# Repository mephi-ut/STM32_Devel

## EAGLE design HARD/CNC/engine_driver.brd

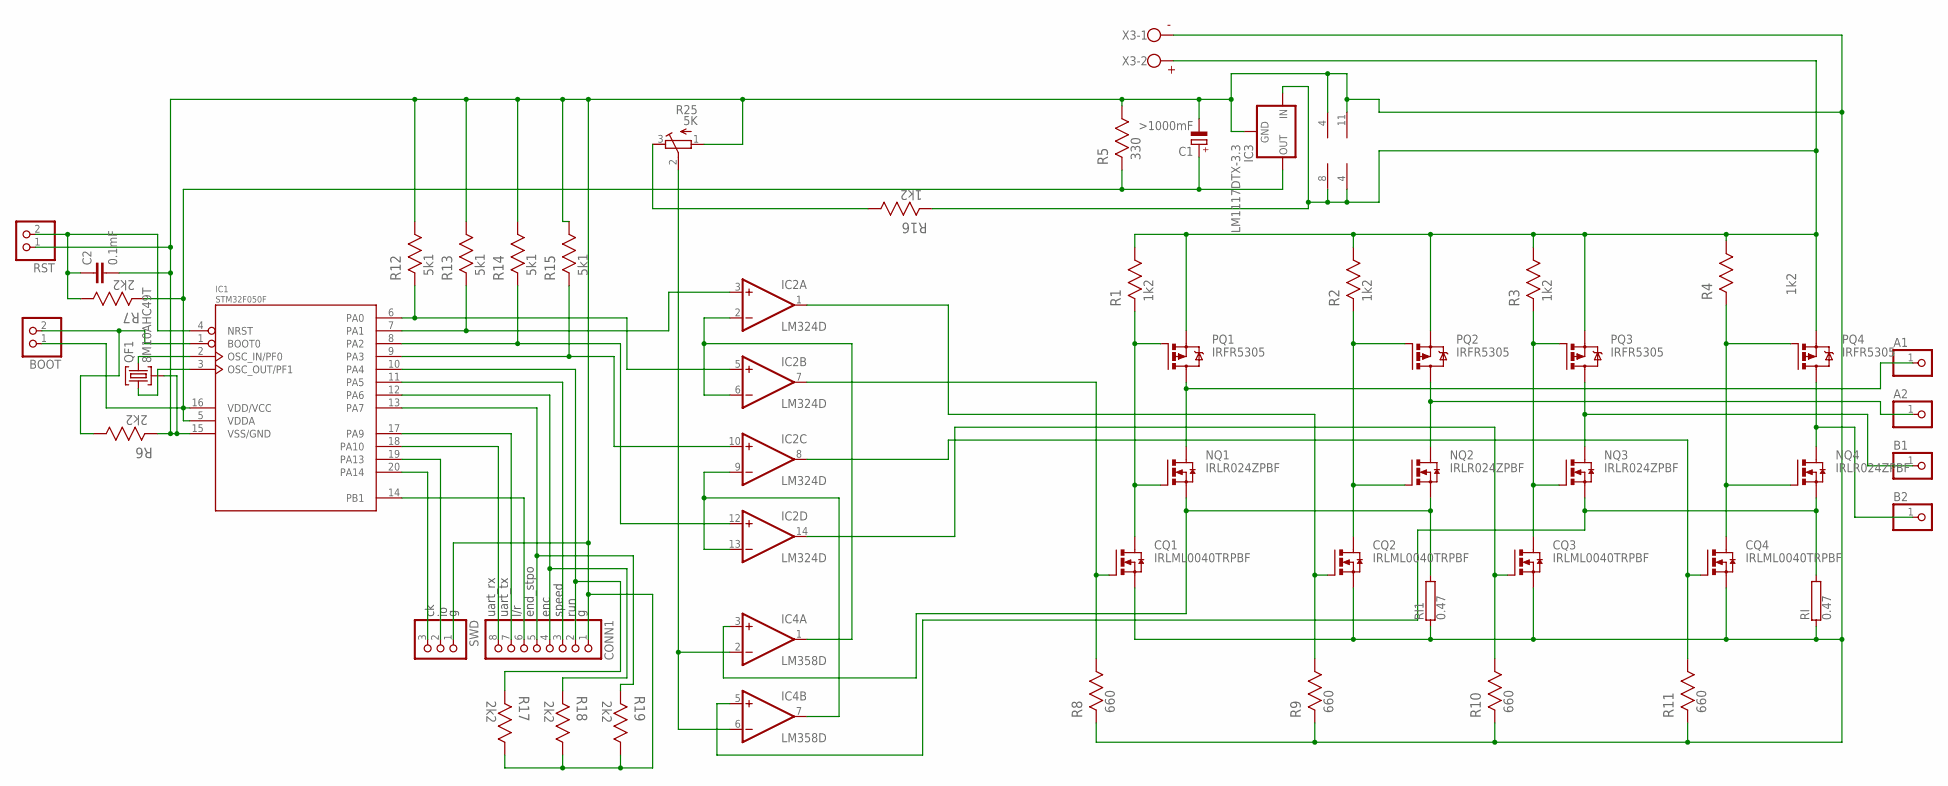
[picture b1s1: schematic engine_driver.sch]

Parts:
A1, A2: PINHD-1X1; 1X01
B1, B2: PINHD-1X1; 1X01
BOOT: PINHD-1X2; 1X02
C1: >1000mF; E2-5
C2: 0.1mF; C1206
CONN1: PINHD-1X8; 1X08
CQ1, CQ2, CQ3, CQ4: IRLML0040TRPBF; MICRO3
IC1: STM32F050F; TSSOP20
IC2: LM324D; SO14
IC3: LM1117DTX-3.3; TO252
IC4: LM358D; SO08
NQ1, NQ2, NQ3, NQ4: IRLR024ZPBF; D-PAK_TO252AA
PQ1, PQ2, PQ3, PQ4: IRFR5305; D-PAK_TO252AA
QF1: 8M10AHC49T; HC49U
R1, R2, R3, R4, R16: 1k2; RESC3216X71N
R5: 330; RESC3216X71N
R6, R7, R17, R18, R19: 2k2; RESC3216X71N
R8, R9, R10, R11: 660; RESC3216X71N
R12, R13, R14, R15: 5k1; RESC3216X71N
R25: 5K; RTRIM5W
RI, RI1: 0.47; HPS947
RST: PINHD-1X2; 1X02
SWD: PINHD-1X3; 1X03
X3: W237-102

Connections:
unnamed: CONN1.7, IC1.17 (PA9)
unnamed: IC4.3 (+IN), NQ1.3 (S), NQ2.3 (S), RI1.2
unnamed: IC2.2 (-IN), IC2.6 (-IN), IC4.1 (OUT)
unnamed: IC1.6 (PA0), IC2.5 (+IN), R12.2
unnamed: IC1.7 (PA1), IC2.3 (+IN), R13.2
unnamed: IC1.8 (PA2), IC2.12 (+IN), R14.2
unnamed: IC1.9 (PA3), IC2.10 (+IN), R15.2
unnamed: CONN1.8, IC1.18 (PA10)
unnamed: C1.-, C2.2, CONN1.1, CQ1.2 (S), CQ2.2 (S), CQ3.2 (S), CQ4.2 (S), IC1.15 (VSS/GND), IC2.11 (V-), IC3.1 (GND), IC4.4 (V-), QF1.2, R5.1, R6.2, R8.2, R9.2, R10.2, R11.2, R12.1, R13.1, R14.1, R15.1, R17.1, R18.1, R19.1, R25.1 (A), RI.1, RI1.1, RST.1, SWD.1, X3.1
unnamed: CQ1.3 (D), NQ1.1 (G), PQ1.1 (G), R1.2
unnamed: CQ4.1 (G), IC2.8 (OUT), R11.1
unnamed: IC4.5 (+IN), NQ3.3 (S), NQ4.3 (S), RI.2
unnamed: CQ3.1 (G), IC2.14 (OUT), R10.1
unnamed: A1.1, NQ1.4 (D), PQ1.4 (D)
unnamed: A2.1, NQ2.4 (D), PQ2.4 (D)
unnamed: B2.1, NQ4.4 (D), PQ4.4 (D)
unnamed: B1.1, NQ3.4 (D), PQ3.4 (D)
unnamed: IC2.9 (-IN), IC2.13 (-IN), IC4.7 (OUT)
unnamed: IC1.20 (PA14), SWD.3
unnamed: R16.1, R25.3 (E)
unnamed: IC1.19 (PA13), SWD.2
unnamed: IC4.2 (-IN), IC4.6 (-IN), R25.2 (S)
unnamed: CONN1.5, IC1.13 (PA7), R19.2
unnamed: CONN1.4, IC1.12 (PA6), R18.2
unnamed: CONN1.3, IC1.11 (PA5)
unnamed: IC1.2 (OSC_IN/PF0), QF1.3
unnamed: IC1.3 (OSC_OUT/PF1), QF1.1
unnamed: C2.1, IC1.4 (NRST), R7.1, RST.2
unnamed: BOOT.2, IC1.1 (BOOT0), R6.1
unnamed: CONN1.2, IC1.10 (PA4), R17.2
unnamed: CONN1.6, IC1.14 (PB1)
unnamed: BOOT.1, C1.+, IC1.5 (VDDA), IC1.16 (VDD/VCC), IC3.TAB (OUT), R5.2, R7.2
unnamed: CQ1.1 (G), IC2.7 (OUT), R8.1
unnamed: IC2.4 (V+), IC3.2 (IN), IC4.8 (V+), PQ1.3 (S), PQ2.3 (S), PQ3.3 (S), PQ4.3 (S), R1.1, R2.1, R3.1, R4.1, R16.2, X3.2
unnamed: CQ2.1 (G), IC2.1 (OUT), R9.1
unnamed: CQ2.3 (D), NQ2.1 (G), PQ2.1 (G), R2.2
unnamed: CQ3.3 (D), NQ3.1 (G), PQ3.1 (G), R3.2
unnamed: CQ4.3 (D), NQ4.1 (G), PQ4.1 (G), R4.2

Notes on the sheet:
uart_rx
uart_tx
end_stpo
enc
speed
run
l/r

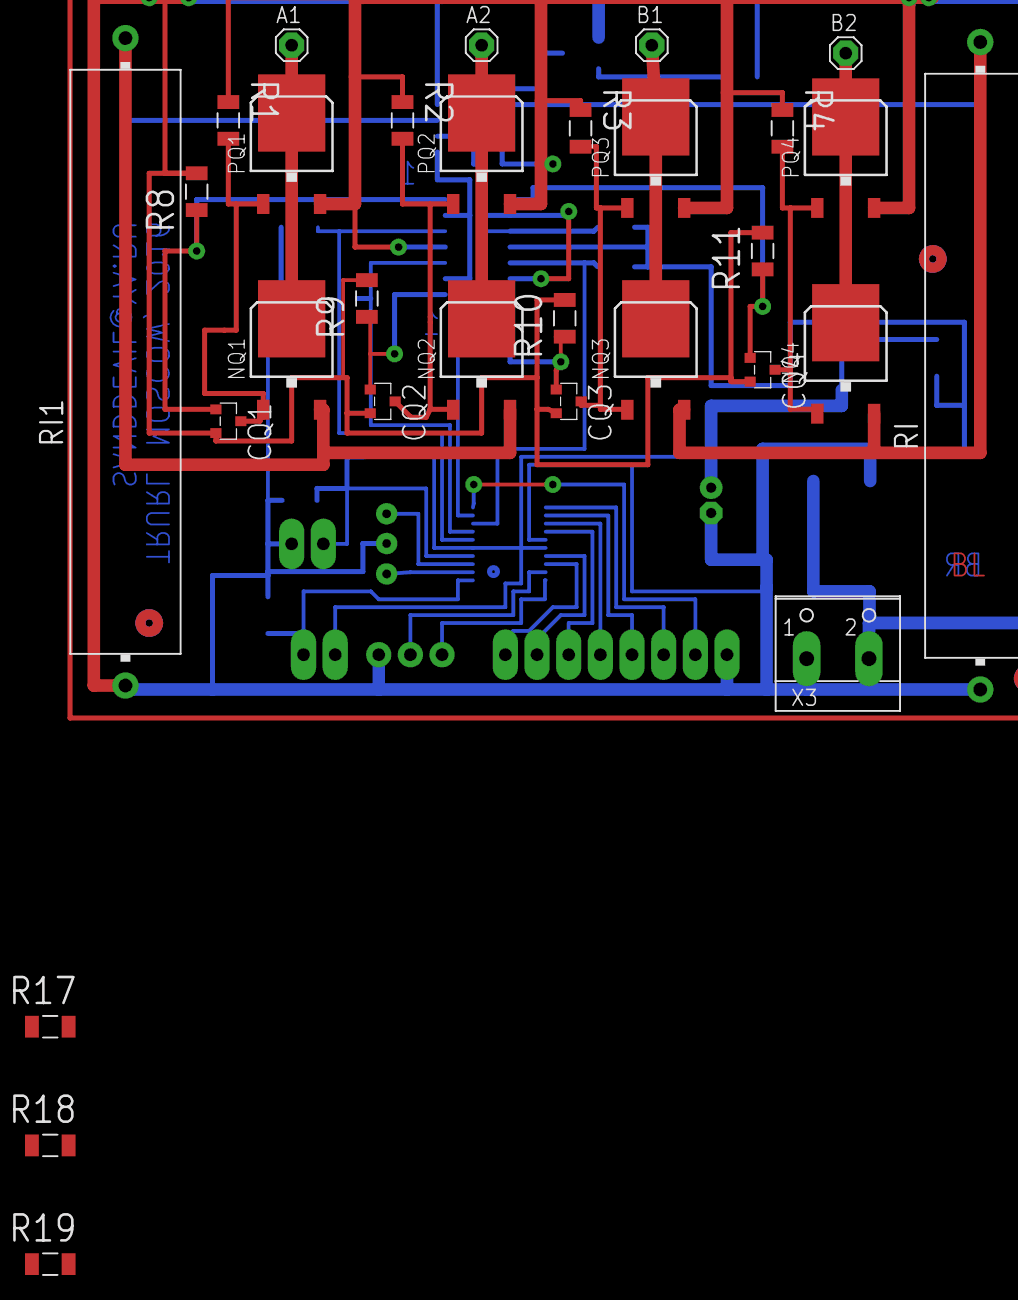
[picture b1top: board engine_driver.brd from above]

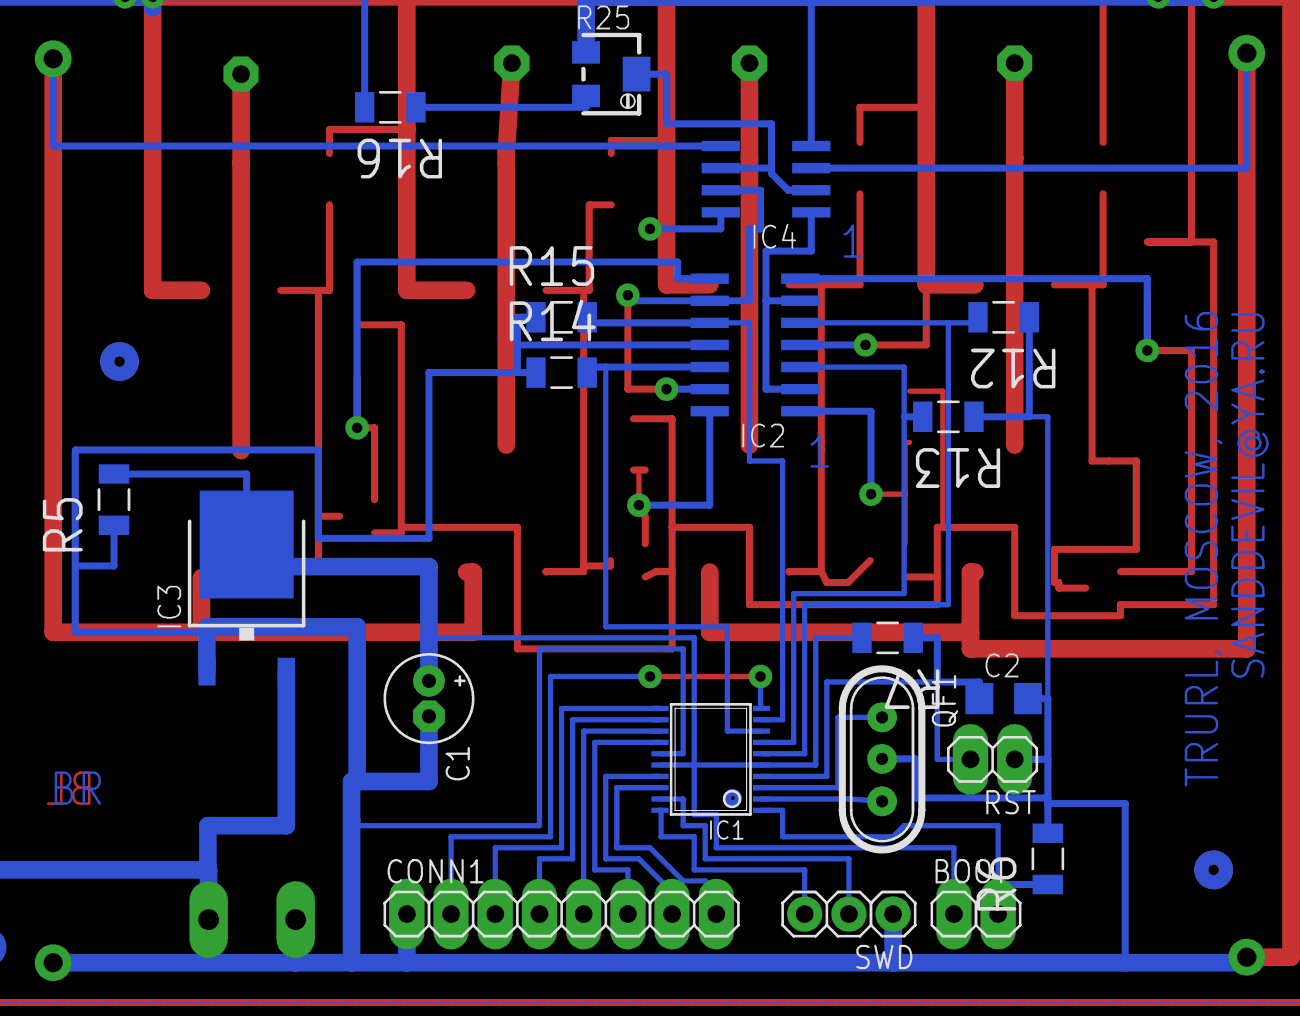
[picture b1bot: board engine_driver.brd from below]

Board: 2 copper layers, 50 parts (20 on the bottom side), 38 nets.

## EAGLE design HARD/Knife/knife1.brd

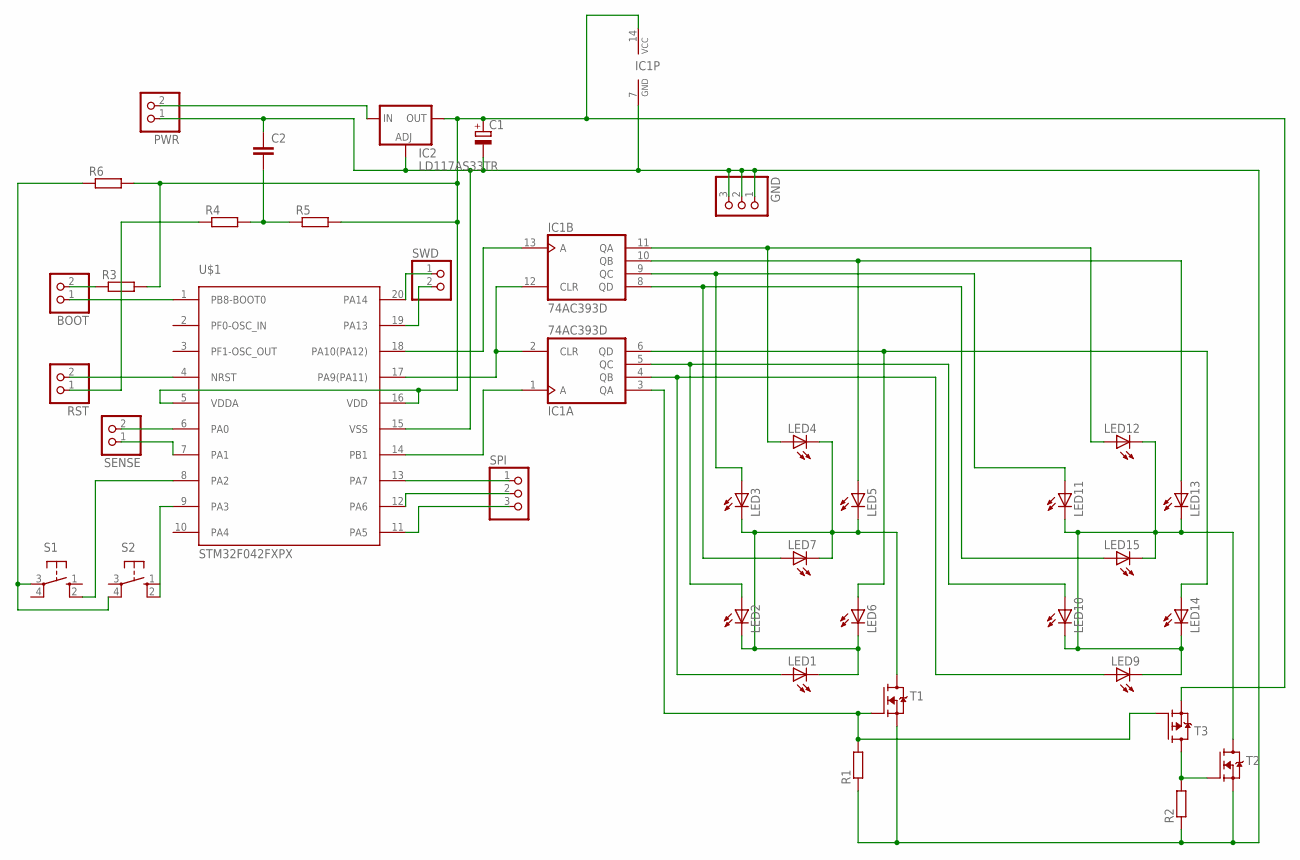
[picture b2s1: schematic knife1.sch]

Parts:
BOOT: PINHD-1X2; 1X02
C1: CPOL-EUSMCD; SMC_D
C2: C-EUC1206; C1206
GND: PINHD-1X3; 1X03
IC1: 74AC393D; SO14
IC2: LD117AS33TR; SOT223
LED1, LED2, LED3, LED4, LED5, LED6, LED7, LED9, LED10, LED11, LED12, LED13, LED14, LED15: LEDSQR2X5; LED2X5
PWR: PINHD-1X2; 1X02
R1, R2, R3, R4, R5, R6: R-EU_M1206; M1206
RST: PINHD-1X2; 1X02
S1, S2: 10-XX; B3F-10XX
SENSE: PINHD-1X2; 1X02
SPI: PINHD-1X3; 1X03
SWD: PINHD-1X2; 1X02
T1, T2: MOSFET-N-SOT23; SOT23
T3: MOSFET-P-SOT23; SOT23
U$1: STM32F042FXPX; TSSOP20

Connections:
unnamed: LED1.K (C), LED2.K (C), LED3.K (C), LED4.K (C), LED5.K (C), LED6.K (C), LED7.K (C), T1.3 (D)
unnamed: R2.2, T2.1 (G), T3.3 (D)
unnamed: IC1.4 (QB), LED1.A, LED9.A
unnamed: LED9.K (C), LED10.K (C), LED11.K (C), LED12.K (C), LED13.K (C), LED14.K (C), LED15.K (C), T2.3 (D)
unnamed: C1.-, C2.1, GND.1, GND.2, GND.3, IC1.7 (GND), IC2.1 (ADJ), PWR.1, R1.1, R2.1, T1.2 (S), T2.2 (S), U$1.15 (VSS)
unnamed: IC1.3 (QA), R1.2, T1.1 (G), T3.1 (G)
unnamed: IC1.5 (QC), LED2.A, LED10.A
unnamed: IC2.3 (IN), PWR.2
unnamed: IC1.6 (QD), LED6.A, LED14.A
unnamed: IC1.2 (CLR), IC1.12 (CLR), U$1.17 (PA9(PA11))
unnamed: IC1.8 (QD), LED7.A, LED15.A
unnamed: SPI.1, U$1.13 (PA7)
unnamed: IC1.9 (QC), LED3.A, LED11.A
unnamed: IC1.13 (A), U$1.18 (PA10(PA12))
unnamed: IC1.10 (QB), LED5.A, LED13.A
unnamed: SPI.2, U$1.12 (PA6)
unnamed: IC1.11 (QA), LED4.A, LED12.A
unnamed: C1.+, IC1.14 (VCC), IC2.4 (OUT), R3.2, R5.2, R6.2, T3.2 (S), U$1.5 (VDDA), U$1.16 (VDD)
unnamed: SPI.3, U$1.11 (PA5)
unnamed: SENSE.2, U$1.6 (PA0)
unnamed: SENSE.1, U$1.7 (PA1)
unnamed: BOOT.1, U$1.1 (PB8-BOOT0)
unnamed: BOOT.2, R3.1
unnamed: RST.2, U$1.4 (NRST)
unnamed: R4.1, RST.1
unnamed: C2.2, R4.2, R5.1
unnamed: R6.1, S1.3, S2.4 (P1)
unnamed: S1.2 (S1), U$1.8 (PA2)
unnamed: S2.2 (S1), U$1.9 (PA3)
unnamed: SWD.1, U$1.20 (PA14)
unnamed: SWD.2, U$1.19 (PA13)
unnamed: IC1.1 (A), U$1.14 (PB1)

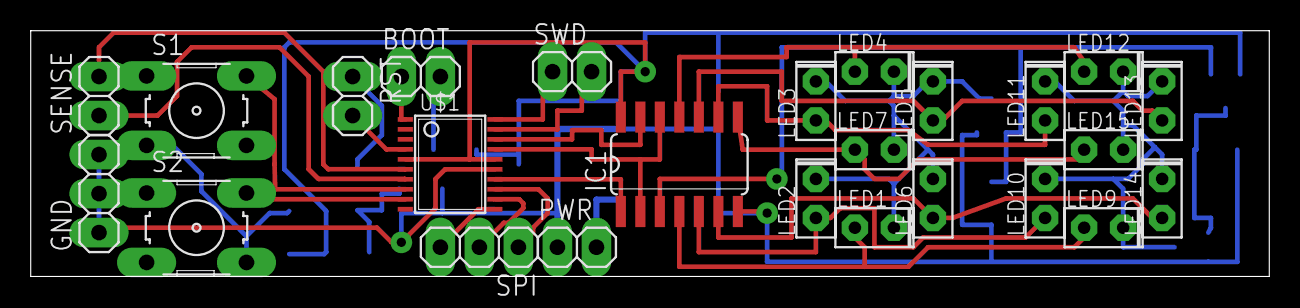
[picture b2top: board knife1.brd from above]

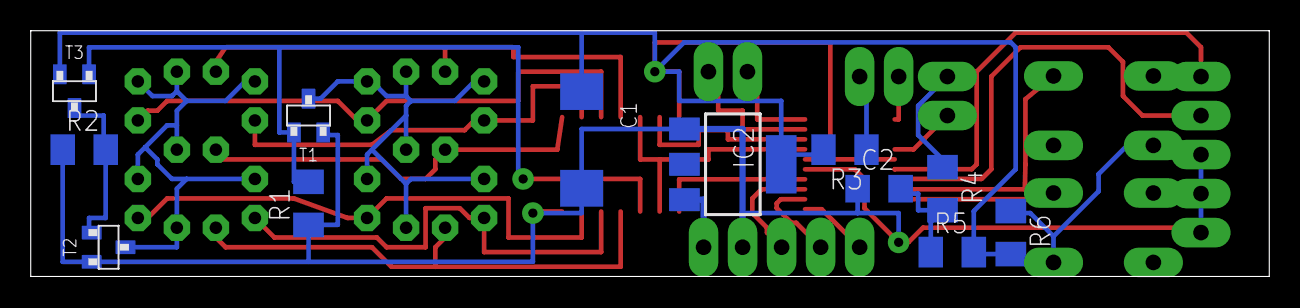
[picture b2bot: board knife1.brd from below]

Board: 2 copper layers, 80.6 x 16.0 mm, 37 parts (12 on the bottom side), 32 nets.

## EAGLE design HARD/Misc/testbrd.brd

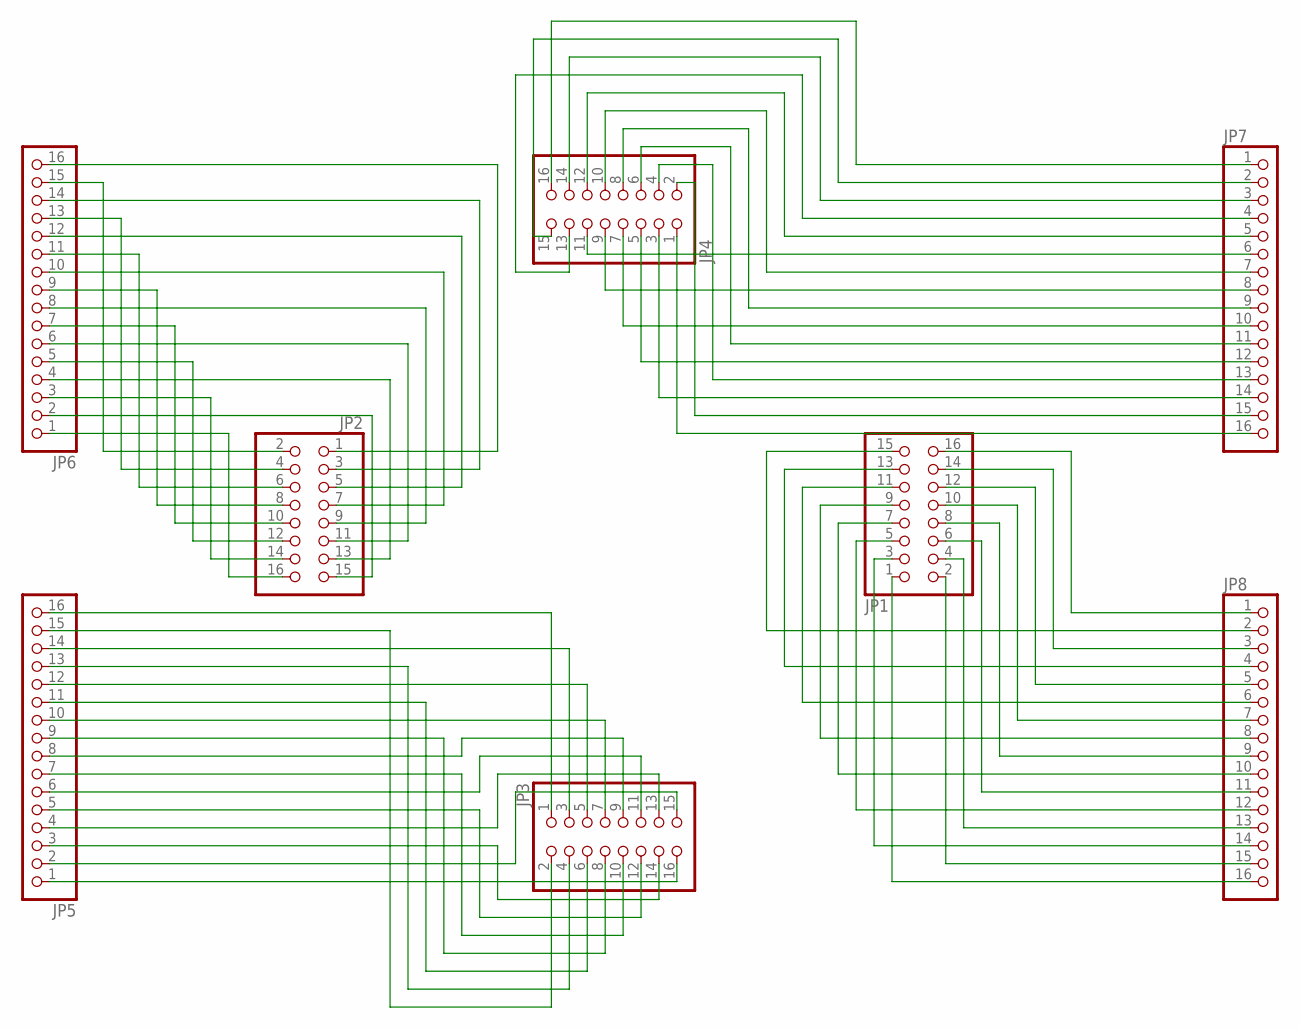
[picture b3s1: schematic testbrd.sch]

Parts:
JP1, JP2, JP3, JP4: PINHD-2X8; 2X08
JP5, JP6, JP7, JP8: PINHD-1X16; 1X16

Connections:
unnamed: JP2.16, JP6.1
unnamed: JP2.15, JP6.2
unnamed: JP2.14, JP6.3
unnamed: JP2.13, JP6.4
unnamed: JP2.12, JP6.5
unnamed: JP2.11, JP6.6
unnamed: JP2.10, JP6.7
unnamed: JP2.9, JP6.8
unnamed: JP2.8, JP6.9
unnamed: JP2.7, JP6.10
unnamed: JP2.6, JP6.11
unnamed: JP2.5, JP6.12
unnamed: JP2.4, JP6.13
unnamed: JP2.3, JP6.14
unnamed: JP2.2, JP6.15
unnamed: JP2.1, JP6.16
unnamed: JP3.16, JP5.1
unnamed: JP3.15, JP5.2
unnamed: JP3.14, JP5.3
unnamed: JP3.13, JP5.4
unnamed: JP3.12, JP5.5
unnamed: JP3.11, JP5.6
unnamed: JP3.10, JP5.7
unnamed: JP3.9, JP5.8
unnamed: JP3.8, JP5.9
unnamed: JP3.7, JP5.10
unnamed: JP3.6, JP5.11
unnamed: JP3.5, JP5.12
unnamed: JP3.4, JP5.13
unnamed: JP3.3, JP5.14
unnamed: JP3.2, JP5.15
unnamed: JP3.1, JP5.16
unnamed: JP1.1, JP8.16
unnamed: JP1.2, JP8.15
unnamed: JP1.3, JP8.14
unnamed: JP1.4, JP8.13
unnamed: JP1.5, JP8.12
unnamed: JP1.6, JP8.11
unnamed: JP1.7, JP8.10
unnamed: JP1.8, JP8.9
unnamed: JP1.9, JP8.8
unnamed: JP1.10, JP8.7
unnamed: JP1.11, JP8.6
unnamed: JP1.12, JP8.5
unnamed: JP1.13, JP8.4
unnamed: JP1.14, JP8.3
unnamed: JP1.15, JP8.2
unnamed: JP1.16, JP8.1
unnamed: JP4.1, JP7.16
unnamed: JP4.2, JP7.15
unnamed: JP4.3, JP7.14
unnamed: JP4.4, JP7.13
unnamed: JP4.5, JP7.12
unnamed: JP4.6, JP7.11
unnamed: JP4.7, JP7.10
unnamed: JP4.8, JP7.9
unnamed: JP4.9, JP7.8
unnamed: JP4.10, JP7.7
unnamed: JP4.11, JP7.6
unnamed: JP4.12, JP7.5
unnamed: JP4.13, JP7.4
unnamed: JP4.14, JP7.3
unnamed: JP4.15, JP7.2
unnamed: JP4.16, JP7.1

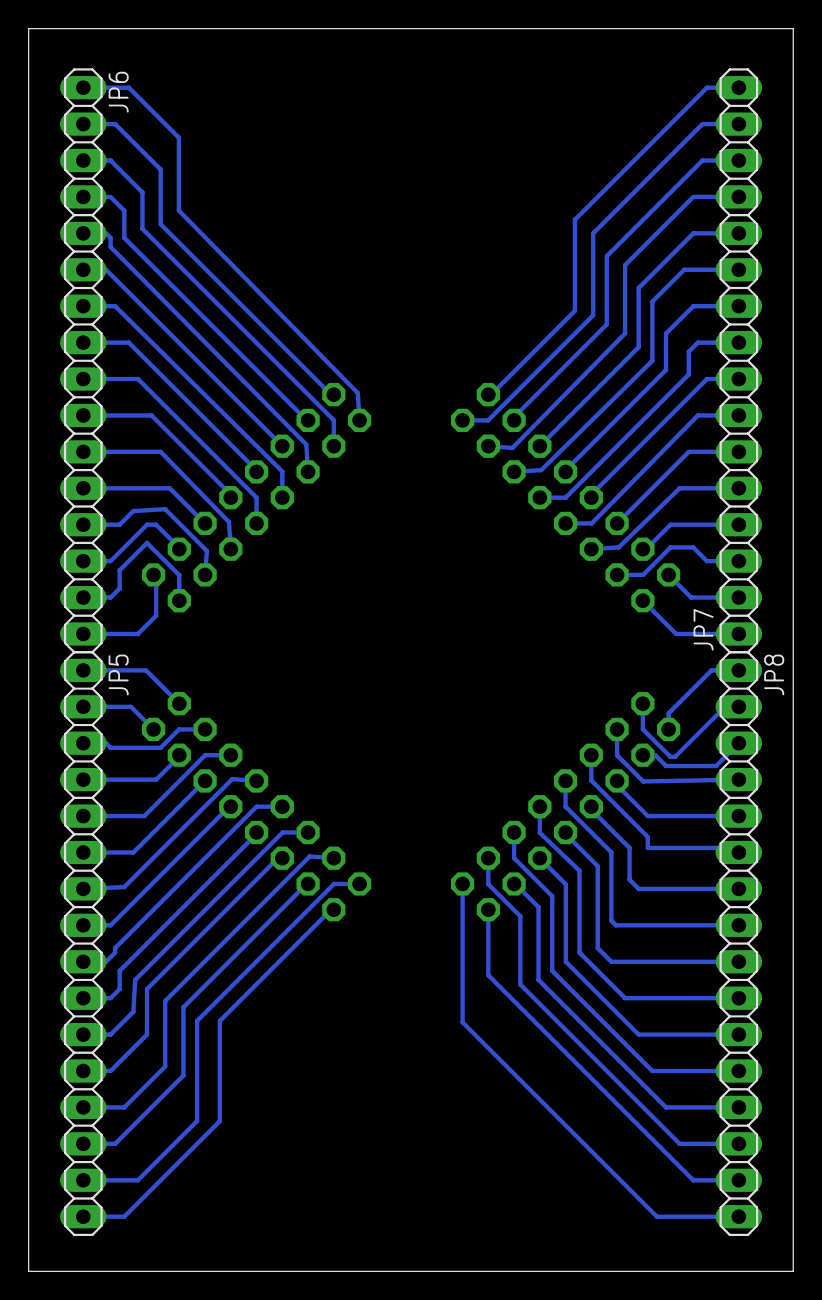
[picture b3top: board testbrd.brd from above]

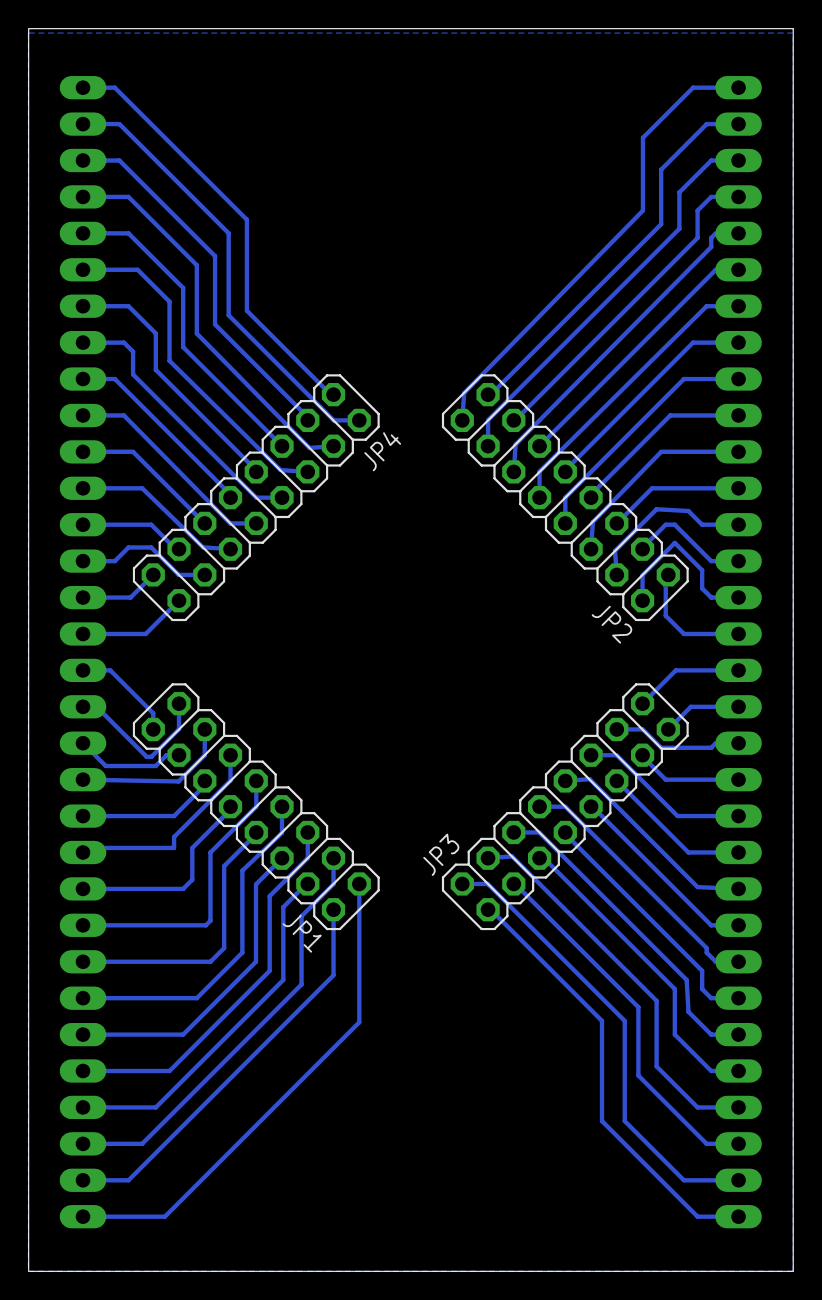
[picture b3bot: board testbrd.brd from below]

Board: 2 copper layers, 53.3 x 86.7 mm, 8 parts (4 on the bottom side), 64 nets.

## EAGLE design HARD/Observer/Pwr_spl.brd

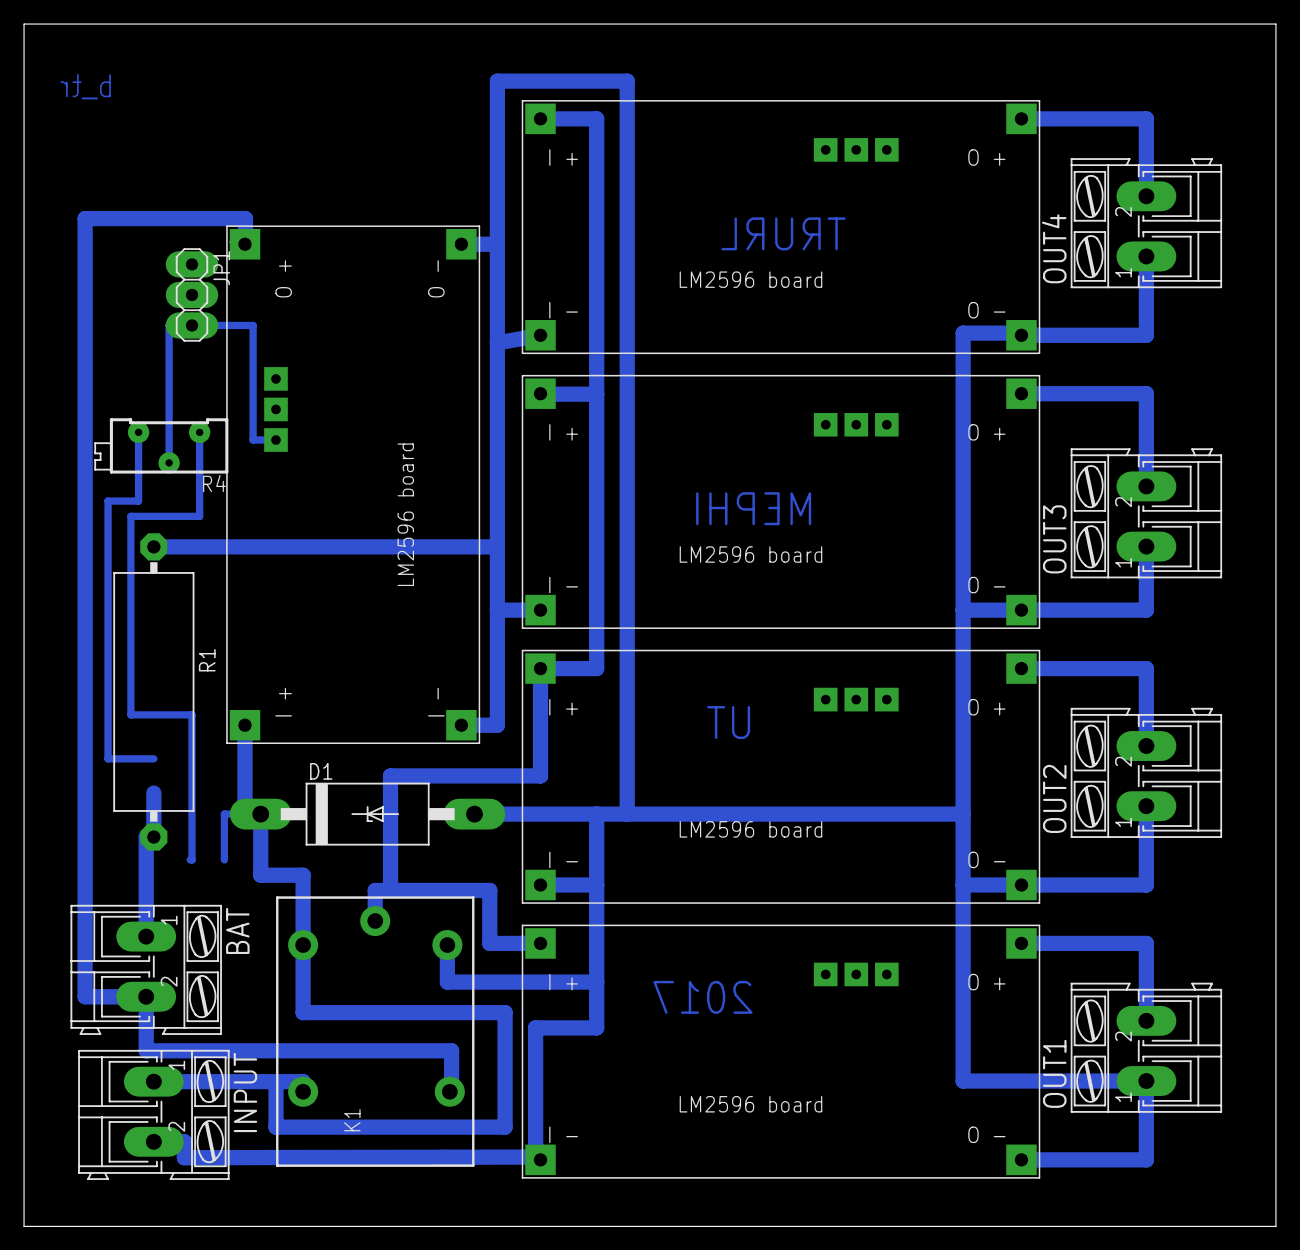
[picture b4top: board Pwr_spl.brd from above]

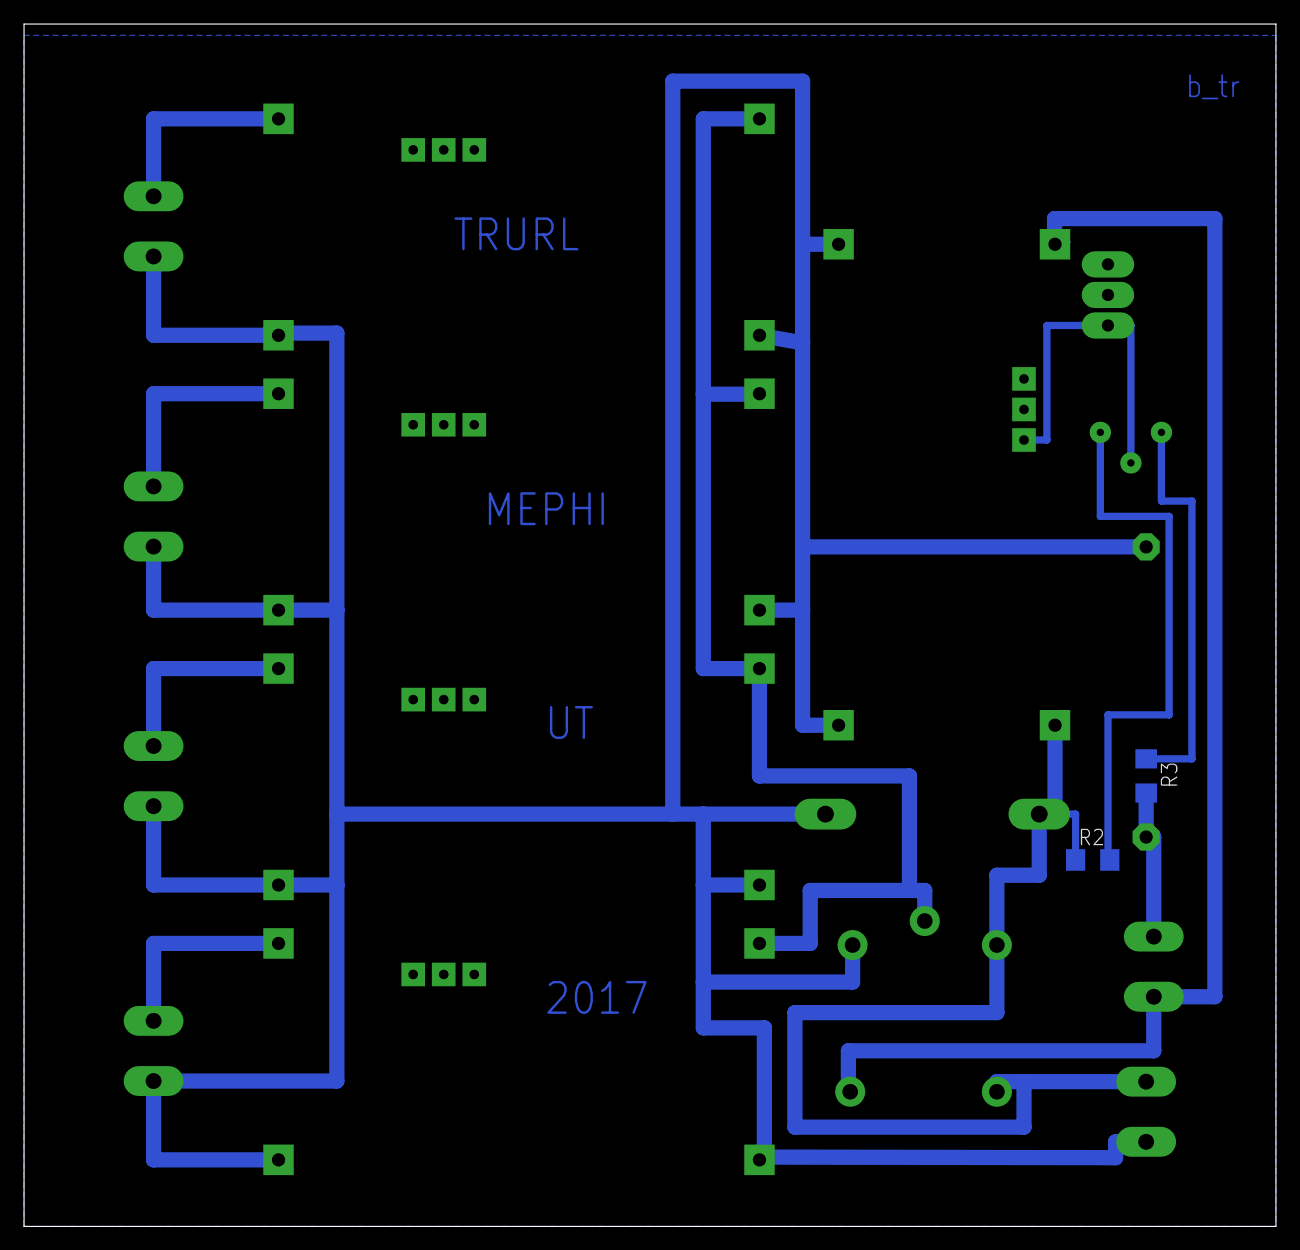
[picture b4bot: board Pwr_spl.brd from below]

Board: 2 copper layers, 104.1 x 100.0 mm, 18 parts (2 on the bottom side), 12 nets.

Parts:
BAT: AK300/2
CHRG: LM2596-BRD; LM2596-BOARD
D1: 15KEXX; CB429-17
INPUT: AK300/2
JP1: 1X03
K1: ZNS5448; ZN5
OUT1, OUT2, OUT3, OUT4: AK300/2
R1: VTA54
R2, R3: 2k; R1206
R4: 1k; RTRIM64Z
U$2, U$3, U$4, U$5: LM2596-BRD; LM2596-BOARD

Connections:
unnamed: CHRG.I_-, CHRG.O_-, D1.A, INPUT.2, K1.A2, OUT1.1, OUT2.1, OUT3.1, OUT4.1, R1.1, U$2.I_-, U$2.O_-, U$3.I_-, U$3.O_-, U$4.I_-, U$4.O_-, U$5.I_-, U$5.O_-
unnamed: CHRG.I_+, D1.C, INPUT.1, K1.14, K1.A1, R2.1
unnamed: K1.11, U$2.I_+, U$3.I_+, U$4.I_+, U$5.I_+
unnamed: BAT.1, R1.2, R3.2
unnamed: BAT.2, CHRG.O_+, K1.12
unnamed: R3.1, R4.3
unnamed: R2.2, R4.1
unnamed: CHRG.P$7, JP1.3, R4.2
unnamed: OUT1.2, U$2.O_+
unnamed: OUT2.2, U$3.O_+
unnamed: OUT3.2, U$4.O_+
unnamed: OUT4.2, U$5.O_+

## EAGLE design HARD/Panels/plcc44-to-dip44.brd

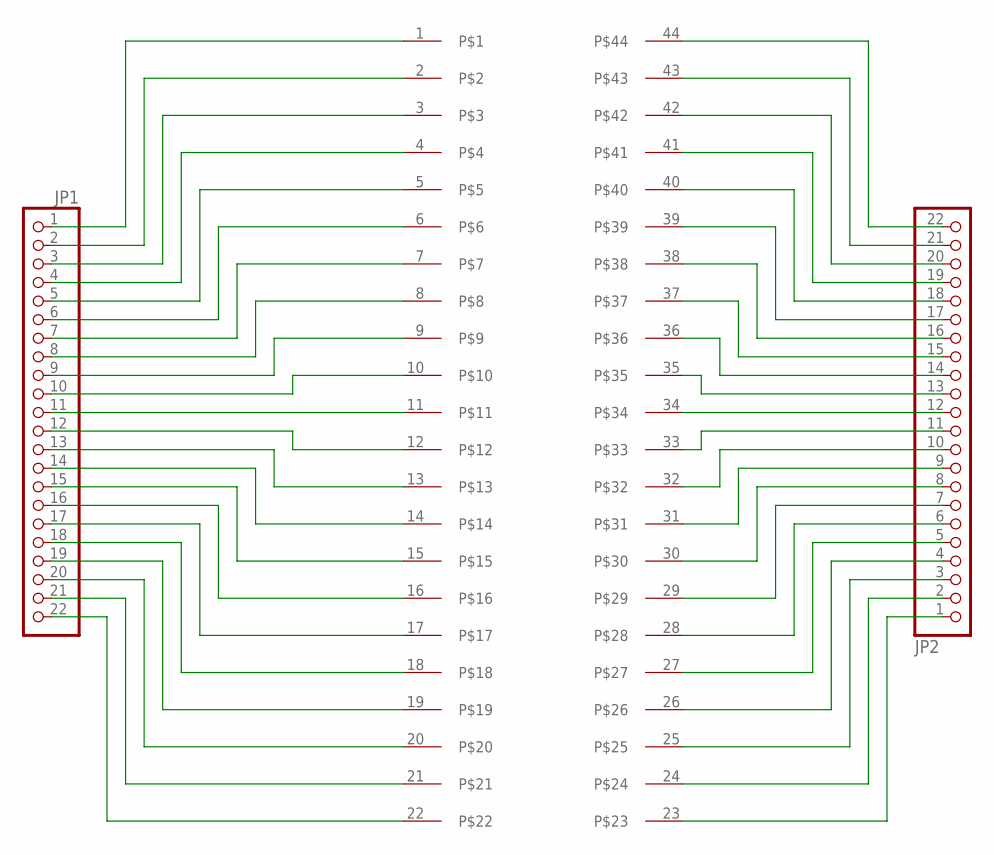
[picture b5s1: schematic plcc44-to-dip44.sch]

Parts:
JP1, JP2: PINHD-1X22; 1X22
U$1: PLCC44-SOCKET; S44

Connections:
unnamed: JP1.1, U$1.1
unnamed: JP1.2, U$1.2
unnamed: JP1.3, U$1.3
unnamed: JP1.4, U$1.4
unnamed: JP1.5, U$1.5
unnamed: JP1.6, U$1.6
unnamed: JP1.7, U$1.7
unnamed: JP1.8, U$1.8
unnamed: JP1.9, U$1.9
unnamed: JP1.10, U$1.10
unnamed: JP1.11, U$1.11
unnamed: JP1.12, U$1.12
unnamed: JP1.13, U$1.13
unnamed: JP1.14, U$1.14
unnamed: JP1.15, U$1.15
unnamed: JP1.16, U$1.16
unnamed: JP1.17, U$1.17
unnamed: JP1.18, U$1.18
unnamed: JP1.19, U$1.19
unnamed: JP1.20, U$1.20
unnamed: JP1.21, U$1.21
unnamed: JP1.22, U$1.22
unnamed: JP2.22, U$1.44
unnamed: JP2.21, U$1.43
unnamed: JP2.20, U$1.42
unnamed: JP2.19, U$1.41
unnamed: JP2.18, U$1.40
unnamed: JP2.17, U$1.39
unnamed: JP2.16, U$1.38
unnamed: JP2.15, U$1.37
unnamed: JP2.14, U$1.36
unnamed: JP2.13, U$1.35
unnamed: JP2.12, U$1.34
unnamed: JP2.11, U$1.33
unnamed: JP2.10, U$1.32
unnamed: JP2.9, U$1.31
unnamed: JP2.8, U$1.30
unnamed: JP2.7, U$1.29
unnamed: JP2.6, U$1.28
unnamed: JP2.5, U$1.27
unnamed: JP2.4, U$1.26
unnamed: JP2.3, U$1.25
unnamed: JP2.2, U$1.24
unnamed: JP2.1, U$1.23

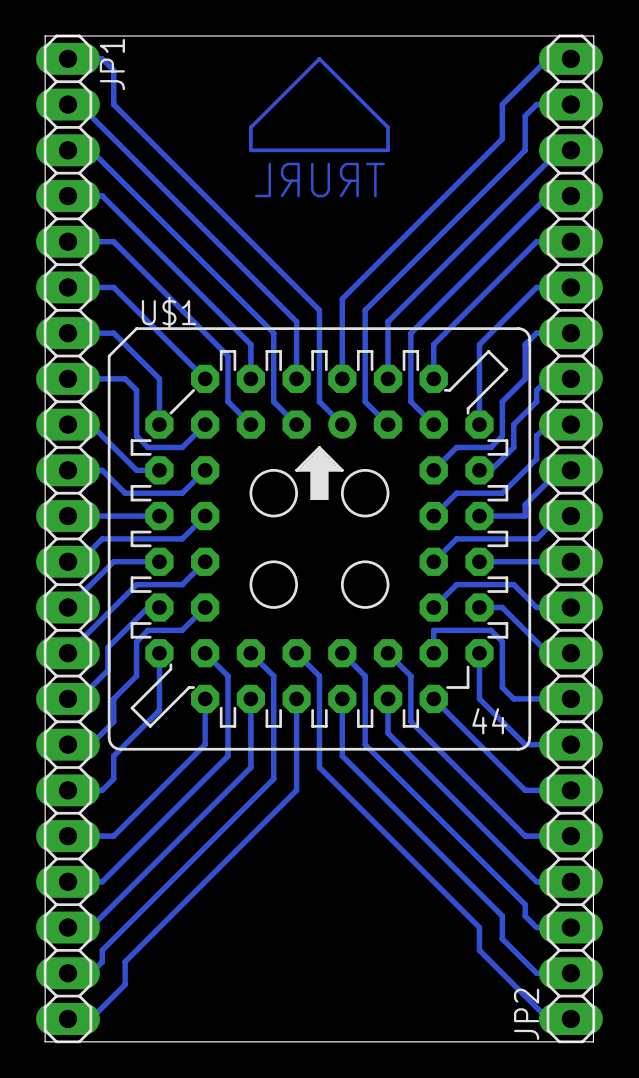
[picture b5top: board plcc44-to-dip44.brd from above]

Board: 2 copper layers, 30.5 x 55.9 mm, 3 parts (0 on the bottom side), 44 nets.
